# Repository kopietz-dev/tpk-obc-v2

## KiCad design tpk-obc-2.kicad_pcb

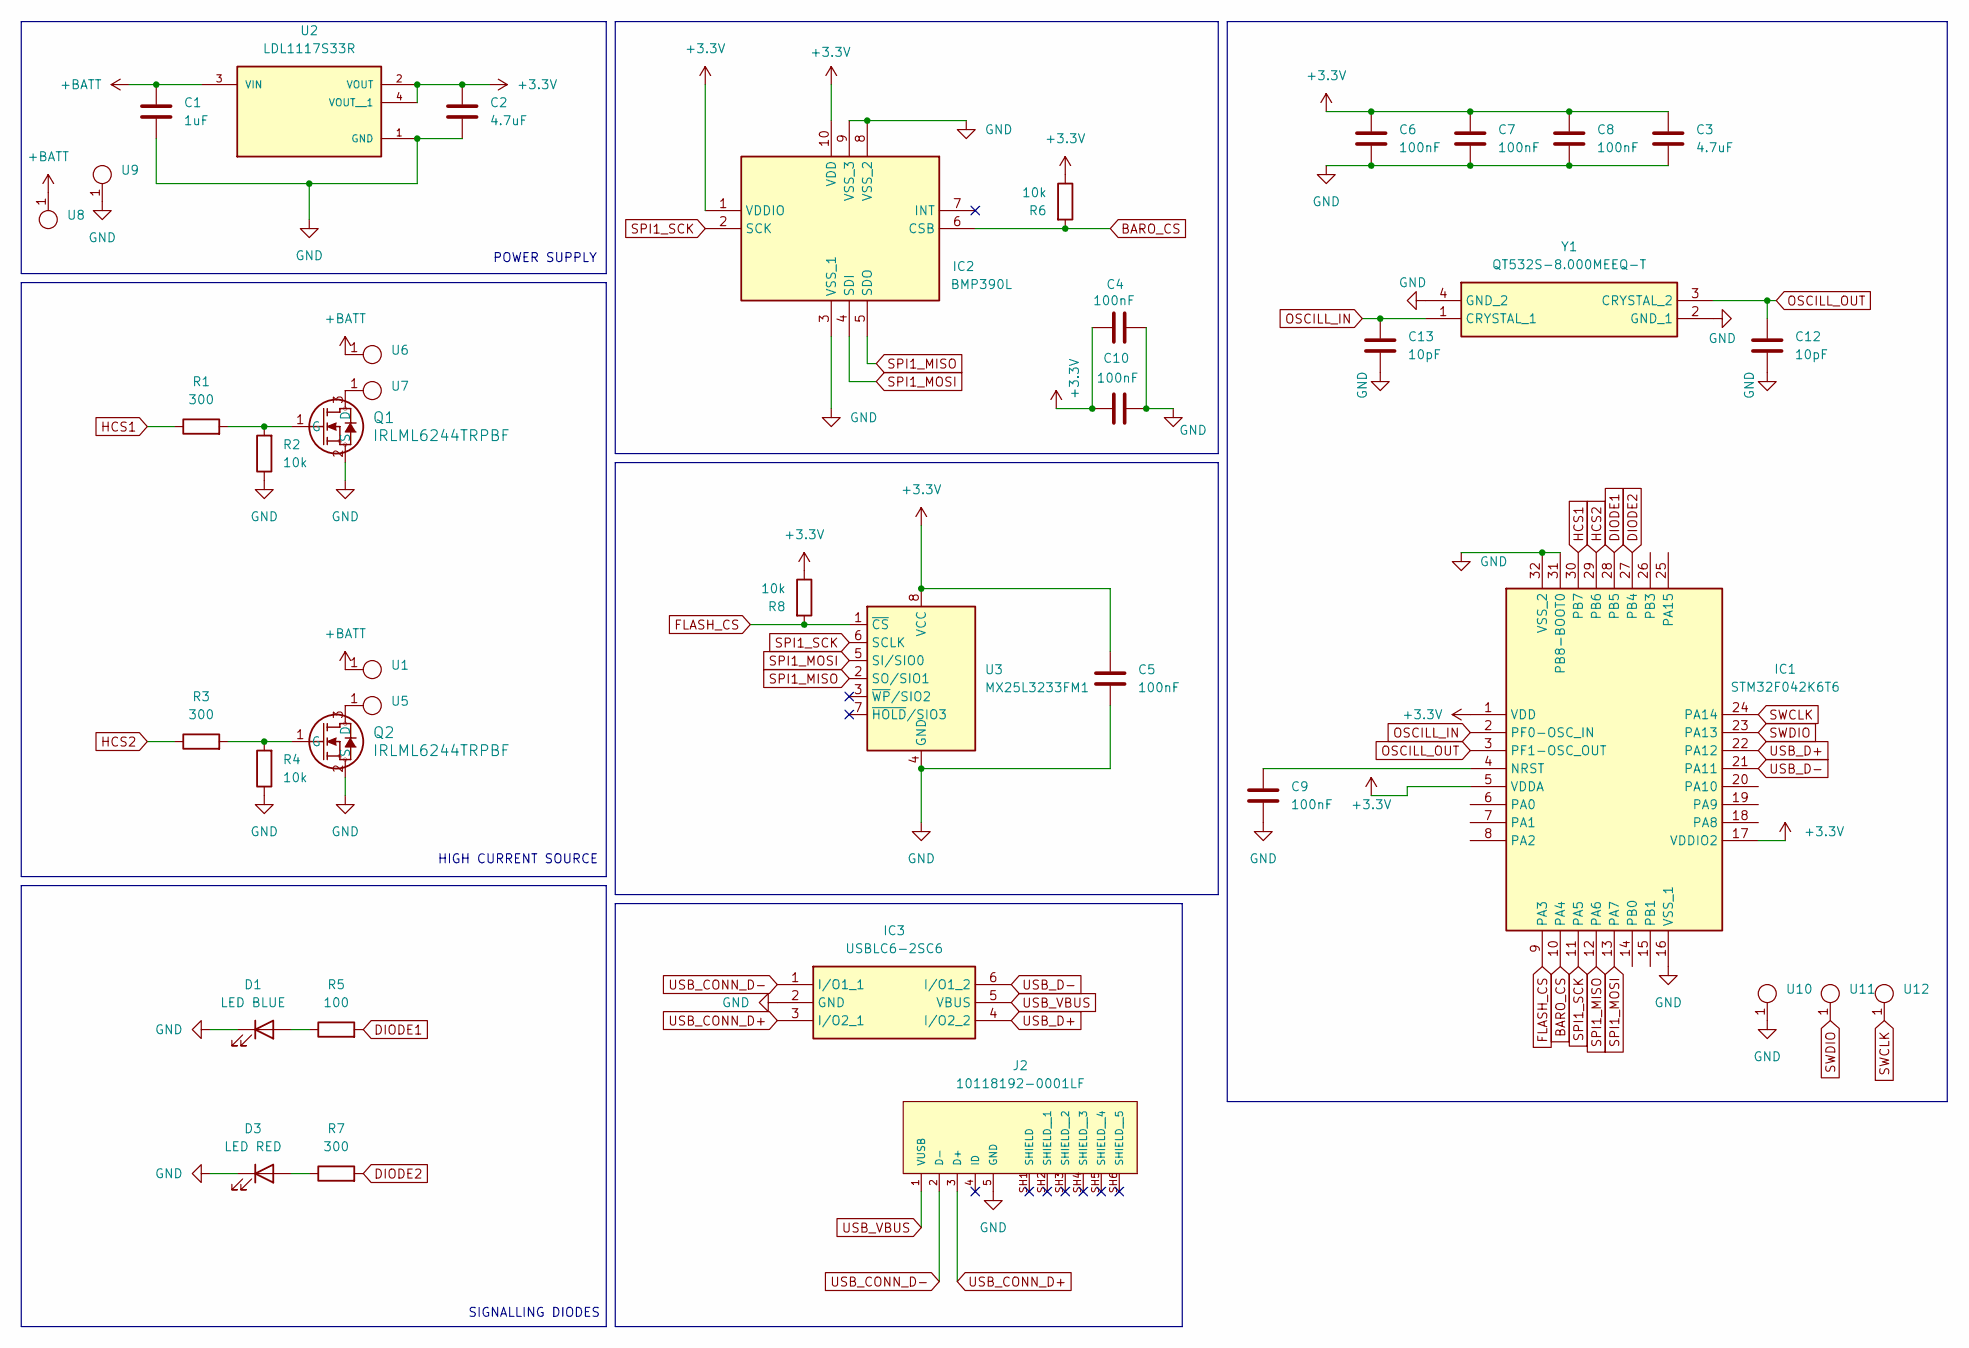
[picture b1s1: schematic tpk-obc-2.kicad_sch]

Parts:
C1: 1uF; C_0805_2012Metric_Pad1.18x1.45mm_HandSolder
C2: 4.7uF; C_0805_2012Metric_Pad1.18x1.45mm_HandSolder
C3: 4.7uF; C_0603_1608Metric
C4, C5, C6, C7, C8, C9, C10: 100nF; C_0603_1608Metric
C12, C13: 10pF; C_0603_1608Metric
D1: LED BLUE; D_0603_1608Metric_Pad1.05x0.95mm_HandSolder
D3: LED RED; D_0603_1608Metric_Pad1.05x0.95mm_HandSolder
IC1: STM32F042K6T6; QFP80P900X900X160-32N; Mouser Part Number 511-STM32F042K6T6
IC2: BMP390L; Mouser Part Number 262-BMP390L
IC3: USBLC6-2SC6; SOT95P280X145-6N; Manufacturer_Part_Number USBLC6-2SC6
J2: 10118192-0001LF; AMPHENOL_10118192-0001LF; PARTREV B
Q1, Q2: IRLML6244TRPBF; PG-SOT23-3-901_INF
R1, R3, R7: 300; C_0603_1608Metric
R2, R4, R6, R8: 10k; C_0603_1608Metric
R5: 100; C_0603_1608Metric
U1, U5, U6, U7, U8, U9, U10, U11, U12: OUTPAD
U2: LDL1117S33R; SOT230P700X180-4N; PARTREV 7
U3: MX25L3233FM1; SOP-8_3.9x4.9mm_P1.27mm
Y1: QT532S-8.000MEEQ-T; QT532S8000MEEQT; Manufacturer_Part_Number QT532S-8.000MEEQ-T

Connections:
+3.3V: C2.1, C3.1, C4.2, C5.1, C6.1, C7.1, C8.1, C10.1, IC1.1 (VDD), IC1.5 (VDDA), IC1.17 (VDDIO2), IC2.1 (VDDIO), IC2.10 (VDD), R6.1, R8.1, U2.2 (VOUT), U2.4 (VOUT__1), U3.8 (VCC)
+BATT: C1.1, U1.1, U2.3 (VIN), U6.1, U8.1
BARO_CS: IC1.10 (PA4), IC2.6 (CSB), R6.2
DIODE1: IC1.28 (PB5), R5.2
DIODE2: IC1.27 (PB4), R7.2
FLASH_CS: IC1.9 (PA3), R8.2, U3.1 (~CS)
GND: C1.2, C2.2, C3.2, C4.1, C5.2, C6.2, C7.2, C8.2, C9.2, C10.2, C12.2, C13.2, D1.1 (K), D3.1 (K), IC1.16 (VSS_1), IC1.31 (PB8-BOOT0), IC1.32 (VSS_2), IC2.3 (VSS_1), IC2.8 (VSS_2), IC2.9 (VSS_3), IC3.2 (GND), J2.5 (GND), Q1.2 (S), Q2.2 (S), R2.1, R4.1, U2.1 (GND), U3.4 (GND), U9.1, U10.1, Y1.2 (GND_1), Y1.4 (GND_2)
HCS1: IC1.30 (PB7), R1.1
HCS2: IC1.29 (PB6), R3.1
unnamed: D1.2 (A), R5.1
unnamed: D3.2 (A), R7.1
unnamed: C9.1, IC1.4 (NRST)
unnamed: Q1.3 (D), U7.1
unnamed: Q1.1 (G), R1.2, R2.2
unnamed: Q2.3 (D), U5.1
unnamed: Q2.1 (G), R3.2, R4.2
OSCILL_IN: C13.1, IC1.2 (PF0-OSC_IN), Y1.1 (CRYSTAL_1)
OSCILL_OUT: C12.1, IC1.3 (PF1-OSC_OUT), Y1.3 (CRYSTAL_2)
SPI1_MISO: IC1.12 (PA6), IC2.5 (SDO), U3.2 (SO/SIO1)
SPI1_MOSI: IC1.13 (PA7), IC2.4 (SDI), U3.5 (SI/SIO0)
SPI1_SCK: IC1.11 (PA5), IC2.2 (SCK), U3.6 (SCLK)
SWCLK: IC1.24 (PA14), U12.1
SWDIO: IC1.23 (PA13), U11.1
USB_CONN_D+: IC3.3 (I/O2_1), J2.3 (D+)
USB_CONN_D-: IC3.1 (I/O1_1), J2.2 (D-)
USB_D+: IC1.22 (PA12), IC3.4 (I/O2_2)
USB_D-: IC1.21 (PA11), IC3.6 (I/O1_2)
USB_VBUS: IC3.5 (VBUS), J2.1 (VUSB)

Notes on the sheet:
SIGNALLING DIODES
HIGH CURRENT SOURCE
POWER SUPPLY

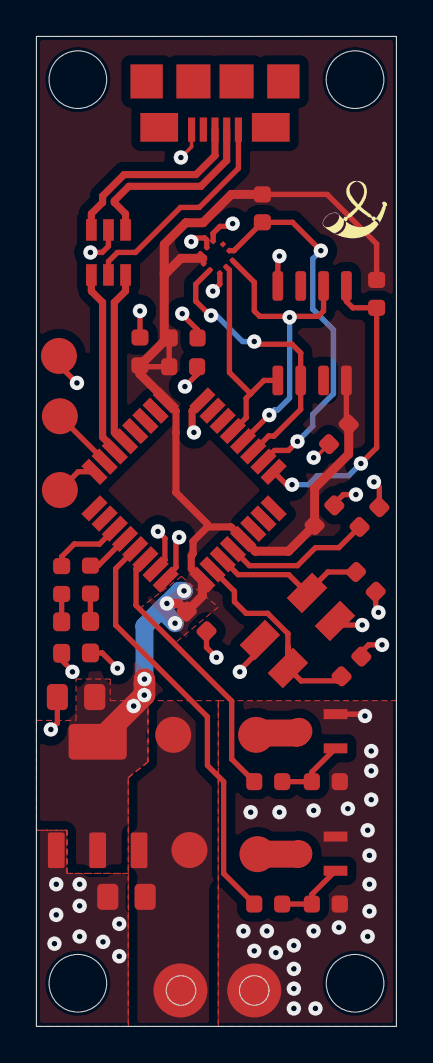
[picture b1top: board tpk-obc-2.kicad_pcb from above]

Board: 2 copper layers, 20.0 x 55.0 mm, 39 parts (0 on the bottom side), 28 nets.
